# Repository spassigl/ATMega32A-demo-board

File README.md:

# ATMega32A demo board
An ATMega32A demo board with exposed GPIO pins, LEDs, tactile switches and a buzzer

## The project
This is a simple ATMega32A board that I used to test some ideas for a bigger project. 
It's a small factor pcb - 88x43mm - with the following features:
- ATMega32A clocked at 16MHz
- 4 layer stackup
- USB-C conneector for power and, with a booloader like urboot, for firmware updates and serial communication. 
- ISP 6-pin connector to flash bootloader or firmware (in case you don't want to use a booloader like urboot or optiboot)
- Power OR-ing - can have both ISP and USB connected
- All the unused GPIO pins are exposed via connectors on the side of the board
- Can use AREF for the ADC pins. AVCC connected via a low pass filter to reduce ADC noise
- SCL/SDA pull-up resistors can be enabled through solder jumpers
- Includes a buzzer, two LEDs, two tactile buttons
- Footprints are optimized for JLCPCB and "Basic" or "Preferred Extended" parts, to lower assembly costs

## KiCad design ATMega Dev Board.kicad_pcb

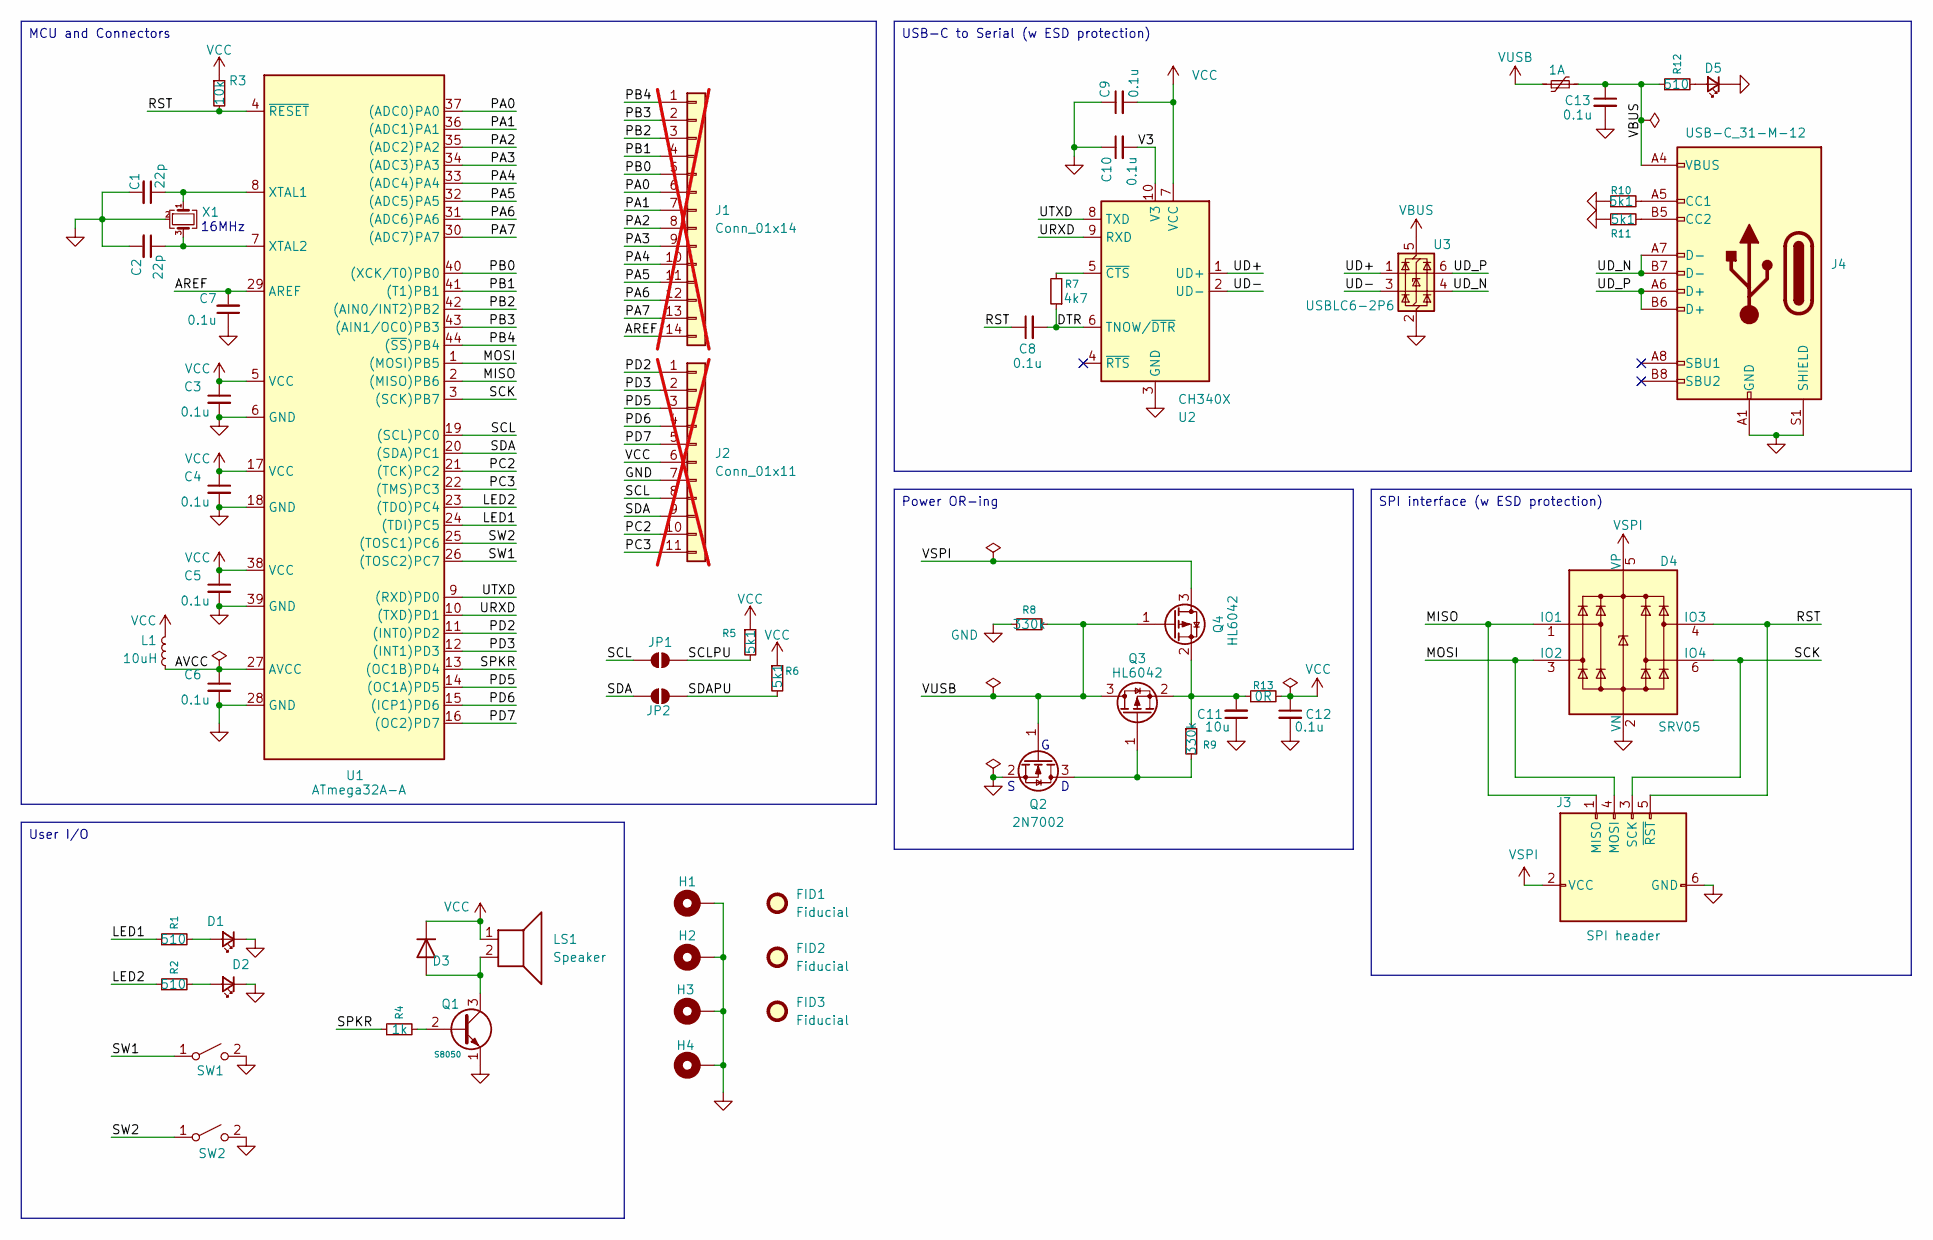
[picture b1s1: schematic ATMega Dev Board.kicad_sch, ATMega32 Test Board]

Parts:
C1, C2: 22p; C_0603_1608Metric; LCSC C1653
C3, C4, C5, C6, C7, C8, C9, C10, C12, C13: 0.1u; C_0603_1608Metric; LCSC C14663
C11: 10u; C_0805_2012Metric; LCSC C15850
D1, D2, D5: LED; LED_0603_1608Metric; LCSC C2286
D3: 1N4001; D_SOD-123; LCSC C7462829
D4: SRV05; SOT-23-6; LCSC C85364
F1: 1A; Fuse_1206_3216Metric; LCSC C69688
FID1, FID2, FID3: Fiducial; Fiducial_1mm_Mask2mm
H1, H2, H3, H4: MountingHole; MountingHole_3.2mm_M3_Pad_Via
J1: Conn_01x14; PinSocket_1x14_P2.54mm_Vertical; LCSC C2905420; not fitted
J2: Conn_01x11; PinSocket_1x11_P2.54mm_Vertical; LCSC C25503117; not fitted
J3: SPI header; IDC-Header_2x03_P2.54mm_Vertical; LCSC C492441
J4: USB-C_31-M-12; USB_C_Receptacle_HRO_TYPE-C-31-M-12; LCSC C165948
JP1, JP2: Jumper_2_Small_Open; SolderJumper-2_P1.3mm_Open_Pad1.0x1.5mm
L1: 10uH; L_0805_2012Metric; LCSC C2909263
LS1: Speaker; Buzzer_MLT-9650; LCSC C96127
Q1: S8050; SOT-23; LCSC C2146
Q2: 2N7002; SOT-23; LCSC C8545
Q3, Q4: HL6042; SOT-23; Part HL6042; LCSC C28646264
R1, R2, R12: 510; R_0603_1608Metric; LCSC C23193
R3: 10k; R_0603_1608Metric; LCSC C25804
R4: 1k; R_0603_1608Metric; LCSC C21190
R5: 5k1; C_0603_1608Metric; LCSC C23186
R6, R10, R11: 5k1; R_0603_1608Metric; LCSC C23186
R7: 4k7; R_0603_1608Metric; LCSC C23162
R8, R9: 330k; R_0603_1608Metric; LCSC C23137
R13: 0R; R_0603_1608Metric; LCSC C21189
SW1, SW2: SW_SPST; Switch_TS-1088-AR02016; LCSC C720477
U1: ATmega32A-A; TQFP-44_10x10mm_P0.8mm; LCSC C5659
U2: CH340X; MSOP-10_3x3mm_P0.5mm; LCSC C84681
U3: USBLC6-2P6; SOT-666; LCSC C15999
X1: 16MHz; Crystal_SMD_3225-4Pin_3.2x2.5mm; LCSC C13738

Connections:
/AREF: C7.2, J1.14, U1.29 (AREF)
/AVCC: C6.1, L1.2, U1.27 (AVCC)
/DTR: C8.2, R7.1, U2.6 (TNOW/~DTR)
/LED1: R1.1, U1.24 ((TDI)PC5)
/LED2: R2.1, U1.23 ((TDO)PC4)
/MISO: D4.1 (IO1), J3.1 (MISO), U1.2 ((MISO)PB6)
/MOSI: D4.3 (IO2), J3.4 (MOSI), U1.1 ((MOSI)PB5)
/PA0: J1.6, U1.37 ((ADC0)PA0)
/PA1: J1.7, U1.36 ((ADC1)PA1)
/PA2: J1.8, U1.35 ((ADC2)PA2)
/PA3: J1.9, U1.34 ((ADC3)PA3)
/PA4: J1.10, U1.33 ((ADC4)PA4)
/PA5: J1.11, U1.32 ((ADC5)PA5)
/PA6: J1.12, U1.31 ((ADC6)PA6)
/PA7: J1.13, U1.30 ((ADC7)PA7)
/PB0: J1.5, U1.40 ((XCK/T0)PB0)
/PB1: J1.4, U1.41 ((T1)PB1)
/PB2: J1.3, U1.42 ((AIN0/INT2)PB2)
/PB3: J1.2, U1.43 ((AIN1/OC0)PB3)
/PB4: J1.1, U1.44 ((~SS)PB4)
/PC2: J2.10, U1.21 ((TCK)PC2)
/PC3: J2.11, U1.22 ((TMS)PC3)
/PD2: J2.1, U1.11 ((INT0)PD2)
/PD3: J2.2, U1.12 ((INT1)PD3)
/PD5: J2.3, U1.14 ((OC1A)PD5)
/PD6: J2.4, U1.15 ((ICP1)PD6)
/PD7: J2.5, U1.16 ((OC2)PD7)
/RST: C8.1, D4.4 (IO3), J3.5 (~RST), R3.2, U1.4 (~RESET)
/SCK: D4.6 (IO4), J3.3 (SCK), U1.3 ((SCK)PB7)
/SCL: J2.8, JP1.1 (A), U1.19 ((SCL)PC0)
/SCLPU: JP1.2 (B), R5.2
/SDA: J2.9, JP2.1 (A), U1.20 ((SDA)PC1)
/SDAPU: JP2.2 (B), R6.2
/SPKR: R4.1, U1.13 ((OC1B)PD4)
/SW1: SW1.1 (A), U1.26 ((TOSC2)PC7)
/SW2: SW2.1 (A), U1.25 ((TOSC1)PC6)
/UD+: U2.1 (UD+), U3.1 (I/O1)
/UD-: U2.2 (UD-), U3.3 (I/O2)
/UD_N: J4.A7 (D-), J4.B7 (D-), U3.4 (I/O2)
/UD_P: J4.A6 (D+), J4.B6 (D+), U3.6 (I/O1)
/URXD: U1.10 ((TXD)PD1), U2.9 (RXD)
/UTXD: U1.9 ((RXD)PD0), U2.8 (TXD)
/V3: C10.2, U2.10 (V3)
GND: C1.2, C2.2, C3.2, C4.2, C5.2, C6.2, C7.1, C9.1, C10.1, C11.1, C12.2, C13.2, D1.1 (K), D2.1 (K), D4.2 (VN), D5.1 (K), H1.1 (1_1), H2.1 (1_1), H3.1 (1_1), H4.1 (1_1), J2.7, J3.6 (GND), J4.A1 (GND), J4.A12 (GND), J4.B1 (GND), J4.B12 (GND), J4.S1 (SHIELD), Q1.1 (E), Q2.2 (S), R8.1, R10.1, R11.1, SW1.2 (B), SW2.2 (B), U1.6 (GND), U1.18 (GND), U1.28 (GND), U1.39 (GND), U2.3 (GND), U3.2 (GND), X1.2 (G), X1.4 (G)
unnamed: D1.2 (A), R1.2
unnamed: D2.2 (A), R2.2
unnamed: D3.2 (A), LS1.2, Q1.3 (C)
unnamed: D5.2 (A), R12.2
unnamed: J4.A5 (CC1), R10.2
unnamed: J4.B5 (CC2), R11.2
unnamed: Q1.2 (B), R4.2
unnamed: Q2.3 (D), Q3.1 (G), R9.2
unnamed: C11.2, Q3.2 (S), Q4.2 (S), R9.1, R13.1
unnamed: C1.1, U1.8 (XTAL1), X1.1
unnamed: C2.1, U1.7 (XTAL2), X1.3
unnamed: R7.2, U2.5 (~CTS)
VBUS: C13.1, F1.2, J4.A4 (VBUS), J4.A9 (VBUS), J4.B4 (VBUS), J4.B9 (VBUS), R12.1, U3.5 (VBUS)
VCC: C3.1, C4.1, C5.1, C9.2, C12.1, D3.1 (K), J2.6, L1.1, LS1.1, R3.1, R5.1, R6.1, R13.2, U1.5 (VCC), U1.17 (VCC), U1.38 (VCC), U2.7 (VCC)
VSPI: D4.5 (VP), J3.2 (VCC), Q4.3 (D)
VUSB: F1.1, Q2.1 (G), Q3.3 (D), Q4.1 (G), R8.2

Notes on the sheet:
16MHz
SPI interface (w ESD protection)
USB-C to Serial (w ESD protection)
User I/O
Power OR-ing
MCU and Connectors

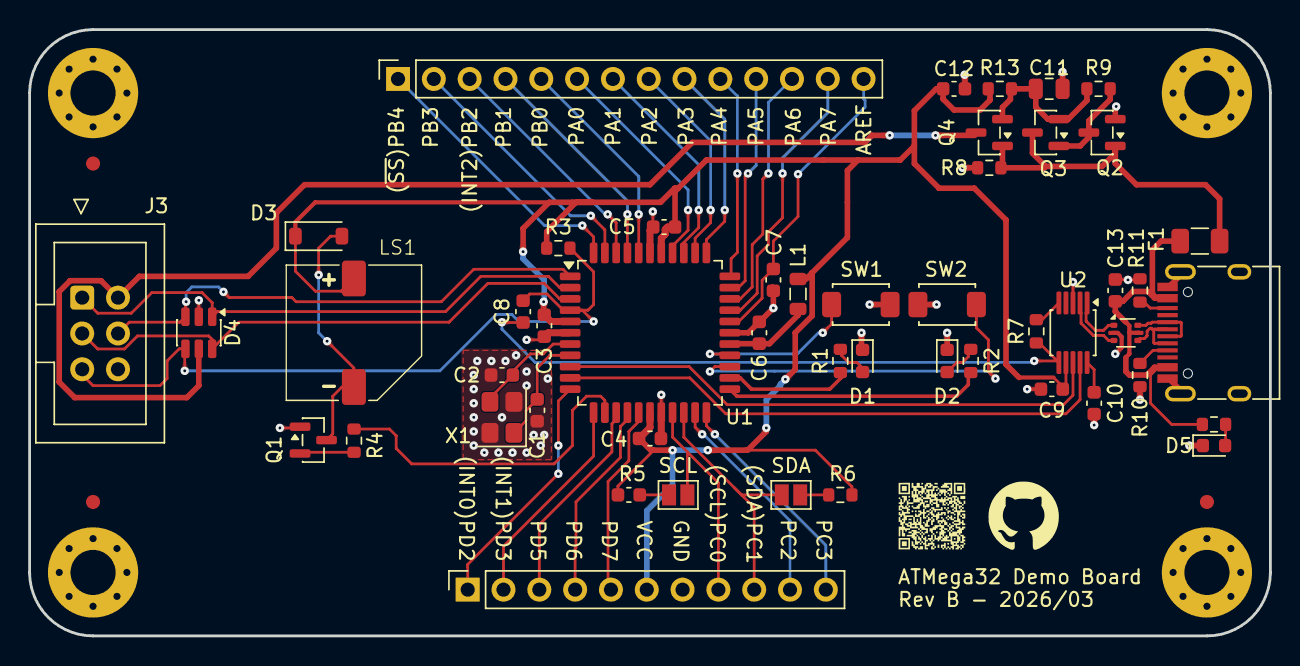
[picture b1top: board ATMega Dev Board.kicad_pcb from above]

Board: 4 copper layers, 88.0 x 43.0 mm, 57 parts (0 on the bottom side), 60 nets.

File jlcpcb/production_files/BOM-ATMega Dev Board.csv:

Comment,Designator,Footprint,LCSC,Quantity
0.1u,"C10,C12,C13,C3,C4,C5,C6,C7,C8,C9",C_0603_1608Metric,C14663,10
0R,R13,R_0603_1608Metric,C21189,1
10k,R3,R_0603_1608Metric,C25804,1
10u,C11,C_0805_2012Metric,C15850,1
10uH,L1,L_0805_2012Metric,C2909263,1
16MHz,X1,Crystal_SMD_3225-4Pin_3.2x2.5mm,C13738,1
1A,F1,Fuse_1206_3216Metric,C69688,1
1N4001,D3,D_SOD-123,C7462829,1
1k,R4,R_0603_1608Metric,C21190,1
22p,"C1,C2",C_0603_1608Metric,C1653,2
2N7002,Q2,SOT-23,C8545,1
330k,"R8,R9",R_0603_1608Metric,C23137,2
4k7,R7,R_0603_1608Metric,C23162,1
510,"R1,R12,R2",R_0603_1608Metric,C23193,3
5k1,"R10,R11,R5,R6",R_0603_1608Metric,C23186,4
ATmega32A-A,U1,TQFP-44_10x10mm_P0.8mm,C5659,1
CH340X,U2,MSOP-10_3x3mm_P0.5mm,C84681,1
HL6042,"Q3,Q4",SOT-23,C28646264,2
LED,"D1,D2,D5",LED_0603_1608Metric,C2286,3
S8050,Q1,SOT-23,C2146,1
SPI header,J3,IDC-Header_2x03_P2.54mm_Vertical,C492441,1
SRV05,D4,SOT-23-6,C85364,1
SW_SPST,"SW1,SW2",Switch_TS-1088-AR02016,C720477,2
Speaker,LS1,Buzzer_MLT-9650,C96127,1
USB-C_31-M-12,J4,USB_C_Receptacle_HRO_TYPE-C-31-M-12,C165948,1
USBLC6-2P6,U3,SOT-666,C15999,1

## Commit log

2026-03-04 Improved VCC routing
2026-03-04 Small footprint changes
2026-03-04 Better traces
2026-03-07 Better layout
2026-03-07 New images
2026-03-07 Removed KiCad backup file
2026-03-07 Updated list of files
2026-03-08 updated production files
2026-03-08 updated images
2026-03-11 updted constraints
2026-03-11 added mounting holes
2026-03-11 better layout and new components
2026-03-11 cosmetic changes
2026-03-12 better vbus power layout
2026-03-12 exposed VCC and GND
2026-03-12 tweaked XTAL traces
2026-03-16 tweaked netclasses
2026-03-16 scl/sda pullups; better vcc filter
2026-03-16 Rev B layout
2026-03-16 tweaked layout
2026-03-16 local libs
2026-03-17 added ADC/AREF components
2026-03-17 changed part#t
2026-03-17 upgraded USB-C routing
2026-03-17 tweaked silkscreen
2026-03-17 added VBUS capacitor
2026-03-17 pdf version of schematic and pcb
2026-03-27 Buzzer example
2026-05-07 fixed CH340X DTR setup
